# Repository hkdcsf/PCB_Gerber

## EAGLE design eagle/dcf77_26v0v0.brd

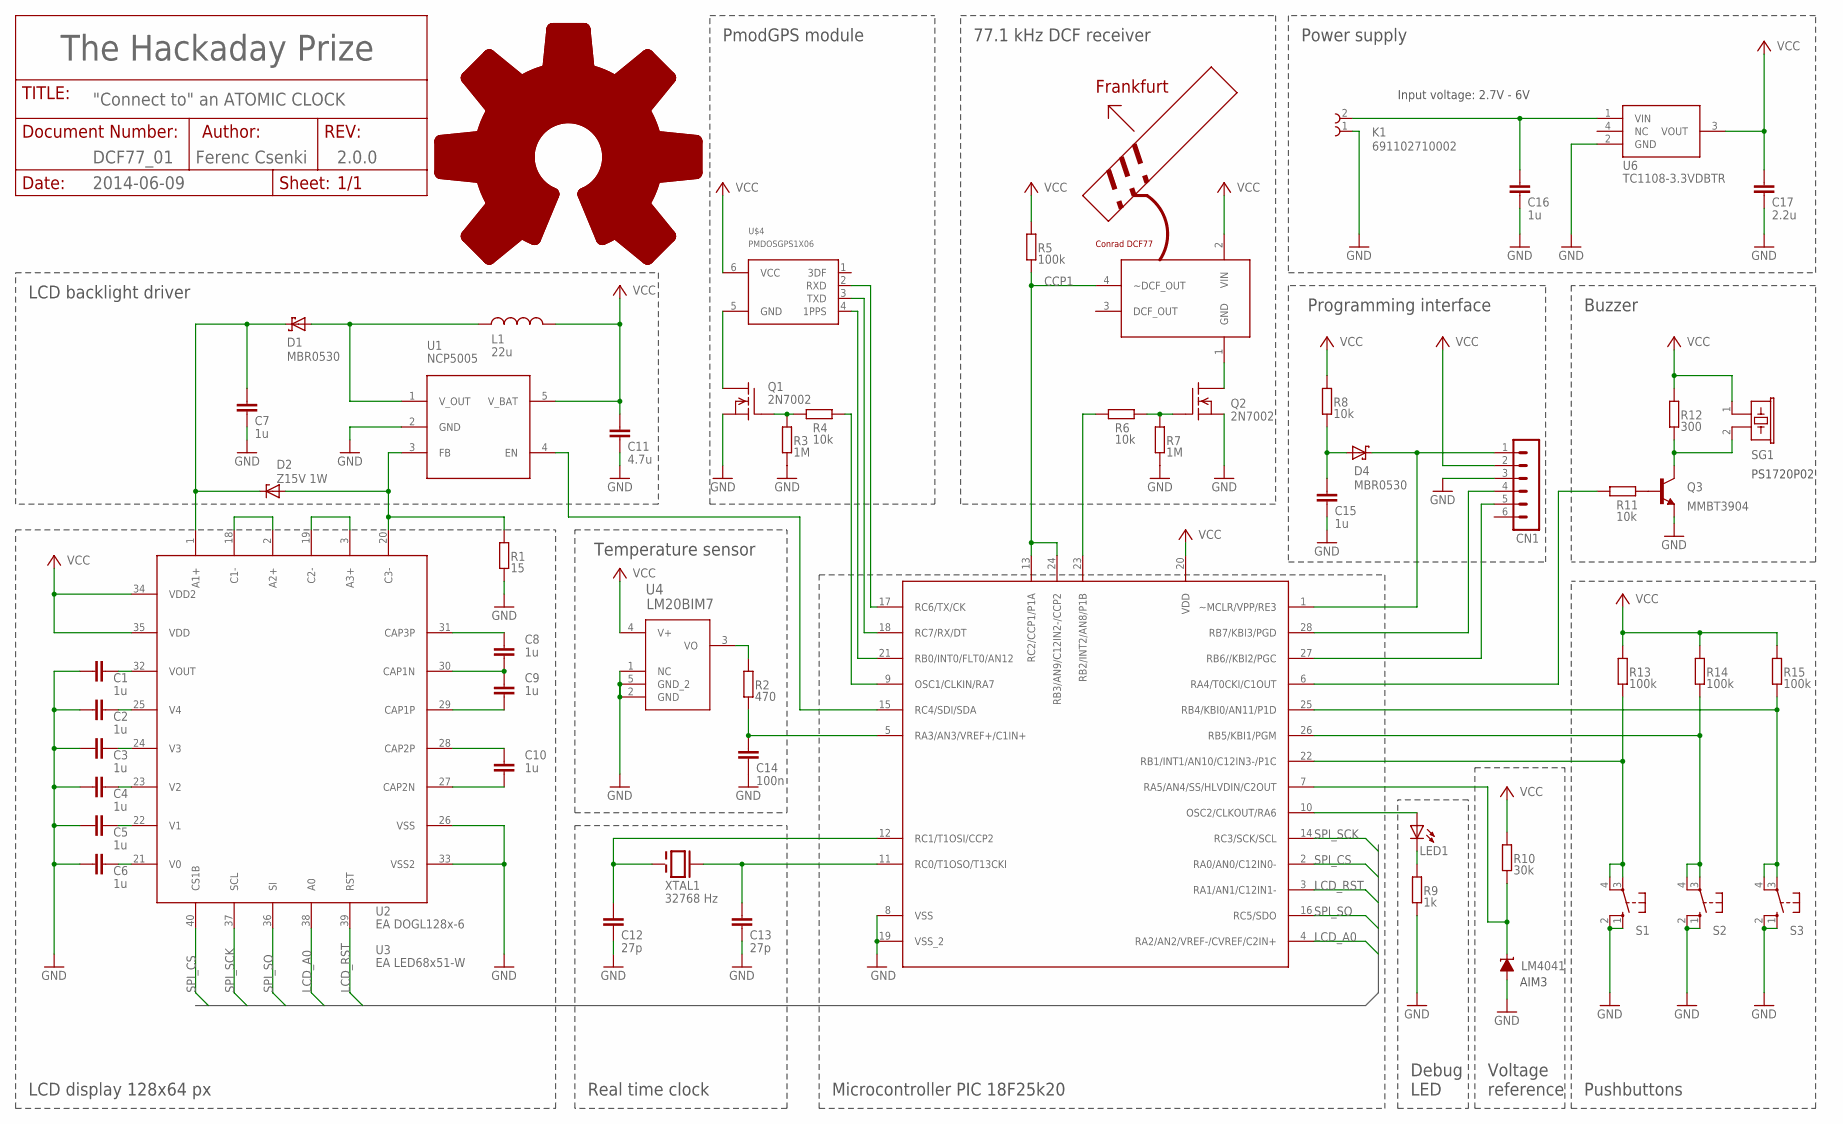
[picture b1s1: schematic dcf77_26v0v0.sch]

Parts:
C1, C2, C3, C4, C5, C6, C7, C8, C9, C10, C15, C16: 1u; C1206K
C11: 4.7u; C1206K
C12, C13: 27p; C1206K
C14: 100n; C1206K
C17: 2.2u; C1206K
CN1: MA06-1
D1, D4: MBR0530; SOD123
D2: Z15V 1W; SMB
K1: 691102710002
K2: 691121710004DCF77_PINHEADER; 1X06
L1: 22u; L1812
LED1: LEDCHIPLED_1206; CHIPLED_1206
LM4041: LM4041A12DBZ; DBZ_R-PDSO-G3
MMBT3904: T1; SOT23-BEC
Q1, Q2: 2N7002; SOT23
R1: 15; R1206
R2: 470; R1206
R3, R7: 1M; R1206
R4, R6, R8, R11: 10k; R1206
R5, R13, R14, R15: 100k; R1206
R9: 1k; R1206
R10: 30k; R1206
R12: 300; R1206
S1, S2, S3: 40-XX; B3F-40XX
SG1: F/EE17P
U1: NCP5005; LTC6900
U4: LM20BIM7; SOT65P240X110-5N
U6: TC1108-3.3VDBTR; SOT223
U$2: DOGL128_DEV; EA_DOGL128-6
U$4: PMDOSGPS1X06; 1X06
U$113: PICDIL28VARIANT; DIL28
XTAL1: 32768 Hz; 38KHZ

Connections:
B1: MMBT3904.C, R12.2, SG1.2
CCP1: K2.4 (~DCF_OUT), R5.1, U$113.13 (RC2/CCP1/P1A), U$113.24 (RB3/AN9/C12IN2-/CCP2)
GND: C1.1, C2.1, C3.1, C4.1, C5.1, C6.1, C7.1, C11.1, C12.1, C13.1, C14.2, C15.1, C16.1, C17.1, CN1.3, K1.1, LM4041.2 (A), MMBT3904.E, Q1.2 (S), Q2.2 (S), R1.1, R3.2, R7.2, R9.1, S1.1 (S), S1.2 (S1), S2.1 (S), S2.2 (S1), S3.1 (S), S3.2 (S1), U1.2 (GND), U4.1 (NC), U4.2 (GND), U4.5 (GND_2), U6.2 (GND), U$2.26 (VSS), U$2.33 (VSS2), U$113.8 (VSS), U$113.19 (VSS_2)
LCD_A0: U$2.38 (A0), U$113.4 (RA2/AN2/VREF-/CVREF/C2IN+)
LCD_RST: U$2.39 (RST), U$113.3 (RA1/AN1/C12IN1-)
unnamed: C10.2, U$2.27 (CAP2N)
unnamed: C10.1, U$2.28 (CAP2P)
unnamed: C9.1, U$2.29 (CAP1P)
unnamed: C8.2, U$2.31 (CAP3P)
unnamed: C3.2, U$2.24 (V3)
unnamed: C8.1, C9.2, U$2.30 (CAP1N)
unnamed: C4.2, U$2.23 (V2)
unnamed: C5.2, U$2.22 (V1)
unnamed: C6.2, U$2.21 (V0)
unnamed: C12.2, U$113.12 (RC1/T1OSI/CCP2), XTAL1.P$1 (1)
unnamed: C13.2, U$113.11 (RC0/T1OSO/T13CKI), XTAL1.P$2 (2)
unnamed: C2.2, U$2.25 (V4)
unnamed: C1.2, U$2.32 (VOUT)
unnamed: K2.1 (GND), Q2.3 (D)
unnamed: CN1.1, D4.C, U$113.1 (~MCLR/VPP/RE3)
unnamed: LED1.A, U$113.10 (OSC2/CLKOUT/RA6)
unnamed: CN1.4, U$113.28 (RB7/KBI3/PGD)
unnamed: CN1.5, U$113.27 (RB6//KBI2/PGC)
unnamed: R13.1, S1.3, S1.4 (P1), U$113.22 (RB1/INT1/AN10/C12IN3-/P1C)
unnamed: R14.1, S2.3, S2.4 (P1), U$113.26 (RB5/KBI1/PGM)
unnamed: R15.1, S3.3, S3.4 (P1), U$113.25 (RB4/KBI0/AN11/P1D)
unnamed: D1.A, L1.1, U1.1 (V_OUT)
unnamed: R4.2, U$113.9 (OSC1/CLKIN/RA7)
unnamed: C7.2, D1.C, D2.C, U$2.1 (A1+)
unnamed: U$2.2 (A2+), U$2.18 (C1-)
unnamed: U$2.3 (A3+), U$2.19 (C2-)
unnamed: LED1.C, R9.2
unnamed: U$4.2 (RXD), U$113.17 (RC6/TX/CK)
unnamed: U1.4 (EN), U$113.15 (RC4/SDI/SDA)
unnamed: D2.A, R1.2, U1.3 (FB), U$2.20 (C3-)
unnamed: R11.2, U$113.6 (RA4/T0CKI/C1OUT)
unnamed: R6.2, U$113.23 (RB2/INT2/AN8/P1B)
unnamed: C16.2, K1.2, U6.1 (VIN)
unnamed: LM4041.1 (C), R10.2, U$113.7 (RA5/AN4/SS/HLVDIN/C2OUT)
unnamed: Q1.3 (D), U$4.5 (GND)
unnamed: Q2.1 (G), R6.1, R7.1
unnamed: C15.2, D4.A, R8.1
unnamed: Q1.1 (G), R3.1, R4.1
unnamed: R2.2, U4.3 (VO)
unnamed: U$4.3 (TXD), U$113.18 (RC7/RX/DT)
unnamed: C14.1, R2.1, U$113.5 (RA3/AN3/VREF+/C1IN+)
unnamed: MMBT3904.B, R11.1
unnamed: U$4.4 (1PPS), U$113.21 (RB0/INT0/FLT0/AN12)
SPI_CS: U$2.40 (CS1B), U$113.2 (RA0/AN0/C12IN0-)
SPI_SCK: U$2.37 (SCL), U$113.14 (RC3/SCK/SCL)
SPI_SO: U$2.36 (SI), U$113.16 (RC5/SDO)
VCC: C11.2, C17.2, CN1.2, K2.2 (VIN), L1.2, R5.2, R8.2, R10.1, R12.1, R13.2, R14.2, R15.2, SG1.1, U1.5 (V_BAT), U4.4 (V+), U6.3 (VOUT), U$2.34 (VDD2), U$2.35 (VDD), U$4.6 (VCC), U$113.20 (VDD)

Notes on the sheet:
EA DOGL128x-6
EA LED68x51-W
Temperature sensor
Real time clock
LCD backlight driver
LCD display 128x64 px
77.1 kHz DCF receiver
Programming interface
Power supply
LED
Pushbuttons
Buzzer
Voltage
reference
AIM3
Microcontroller PIC 18F25k20
PS1720P02
"Connect to" an ATOMIC CLOCK
2014-06-09
2.0.0
DCF77_01
The Hackaday Prize
Ferenc Csenki
Input voltage: 2.7V - 6V
PmodGPS module
Debug

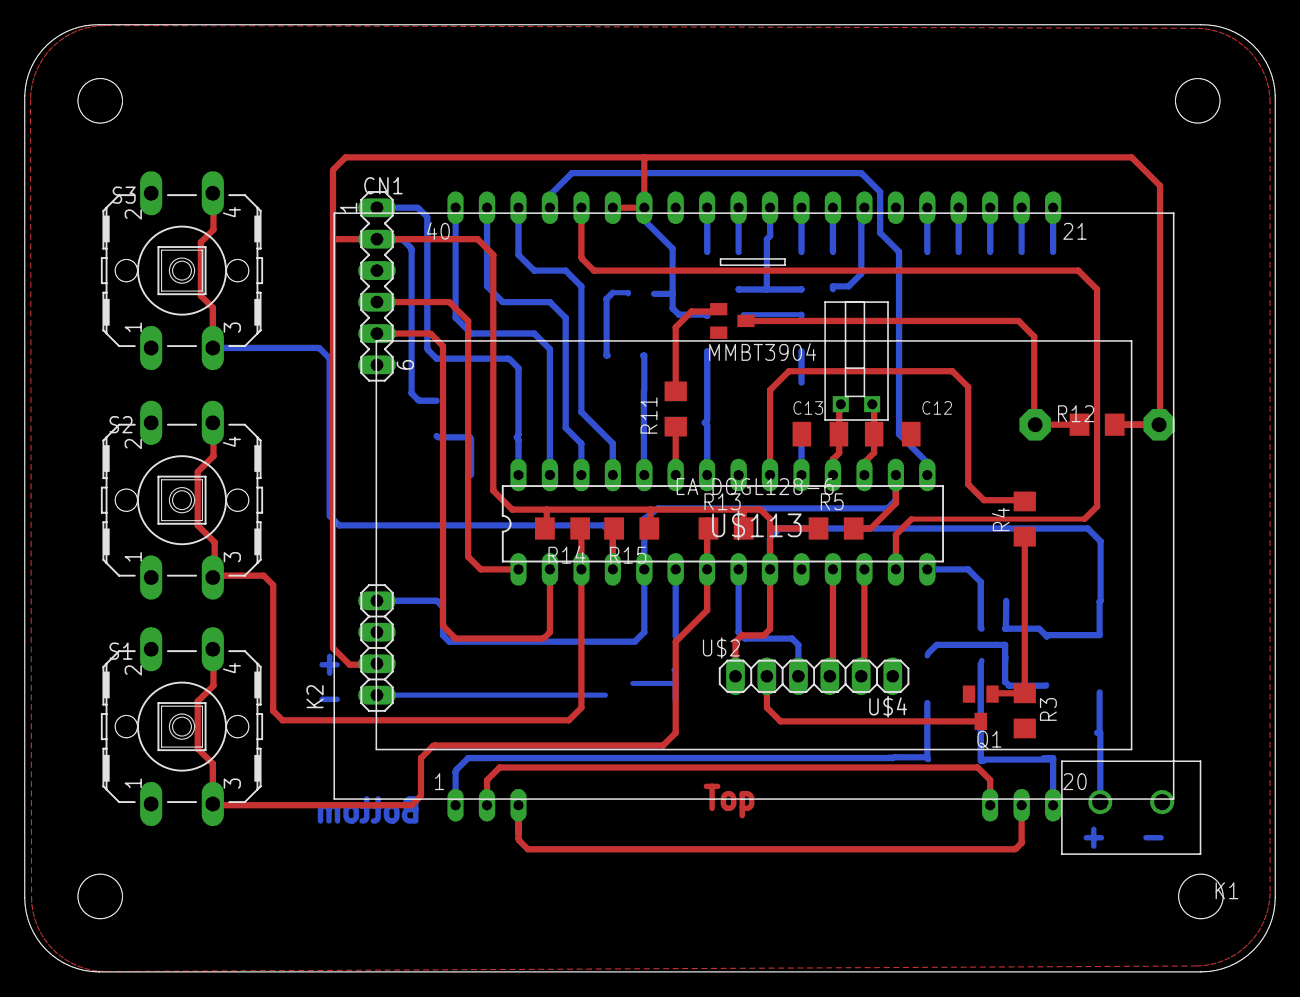
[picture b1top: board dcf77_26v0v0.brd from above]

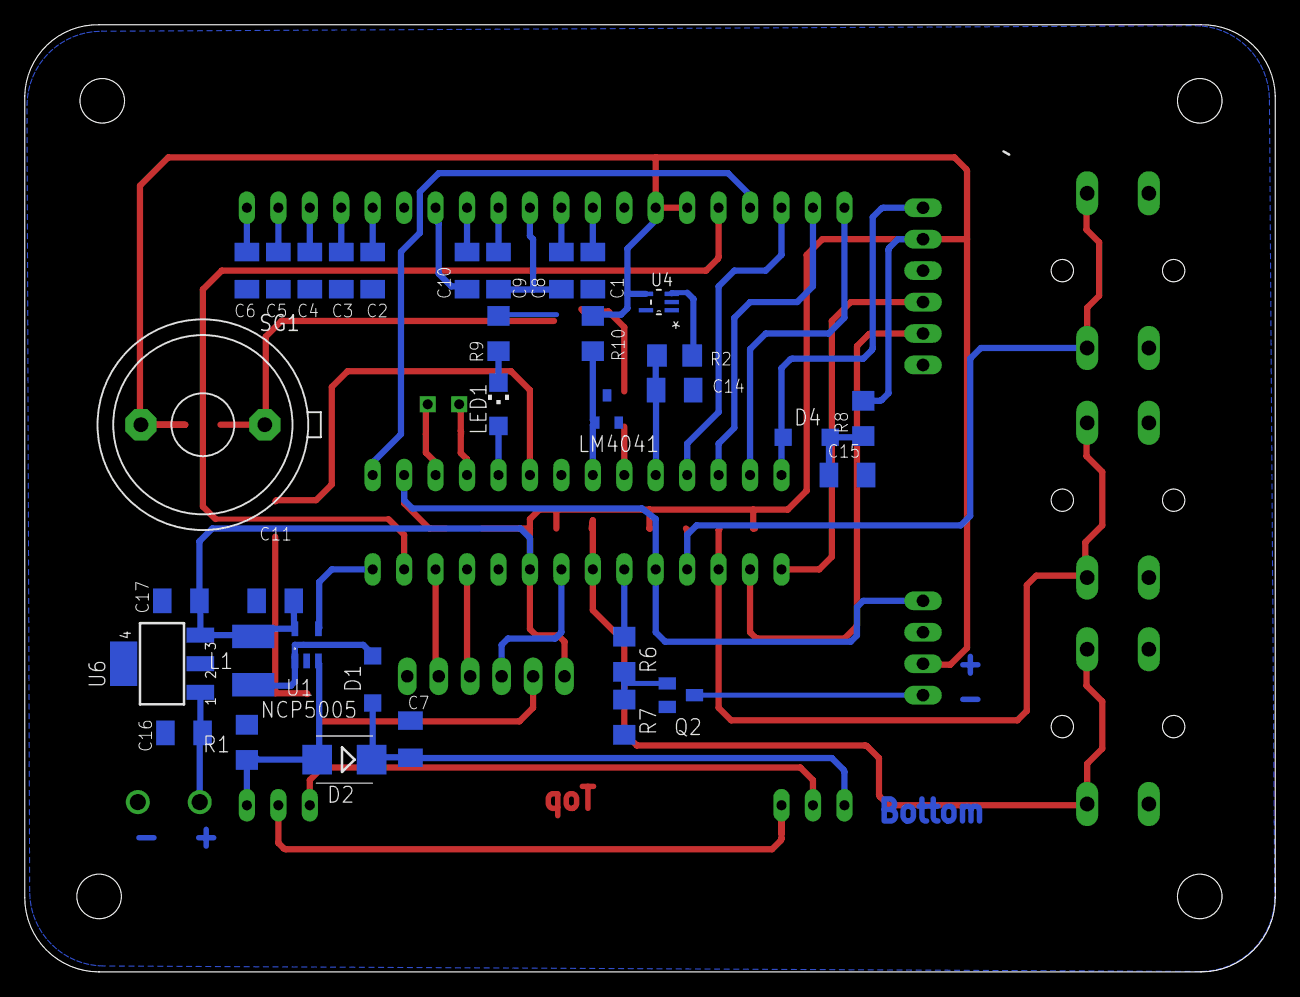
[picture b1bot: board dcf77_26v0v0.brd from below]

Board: 2 copper layers, 101.0 x 76.5 mm, 56 parts (34 on the bottom side), 52 nets.

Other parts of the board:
U$3: OSHW_8X350_NOTEXT

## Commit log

2014-07-12 :tada: Added .gitattributes & .gitignore files
2014-07-12 Gerber files
    Gerber files
2014-07-14 Eagle files
    Eagle files

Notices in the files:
parts and their libraries:
Wuerth_Elektronik_eiCan_Terminal_Blocks_: Copyright: Würth Elektronik
